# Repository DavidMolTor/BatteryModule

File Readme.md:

# USB-C Battery Module

A compact and reliable power module for battery-powered electronics.

## Introduction

This module is designed to be used in guitars and effect pedals as a rechargeable supply with minimal output voltage ripple.

The module contains a TP4056 charging IC and a voltage regulation stage consisting of a TLV61048 boost converter and a TLV76701 linear regulator for further smoothing of the output voltage.

It is designed for 9V output voltage, although it can be configured by adjusting a couple of resistor dividers. It also has PH connectors for charging, battery and output to be able to adapt it to different use cases.

## Features

 - Independent voltage monitor for overdischarge control.

 - 9V output configurable via resistor dividers.

 - Available pin for battery disconnection.

 - LED indicators for charging status display.

 - Soldered USB-C connector for charging.

 - PH connectors for battery, charging and output.

 - Large package sizes for easy hand-soldering.

 - Tested continuous 500mA output and 1A charging current.

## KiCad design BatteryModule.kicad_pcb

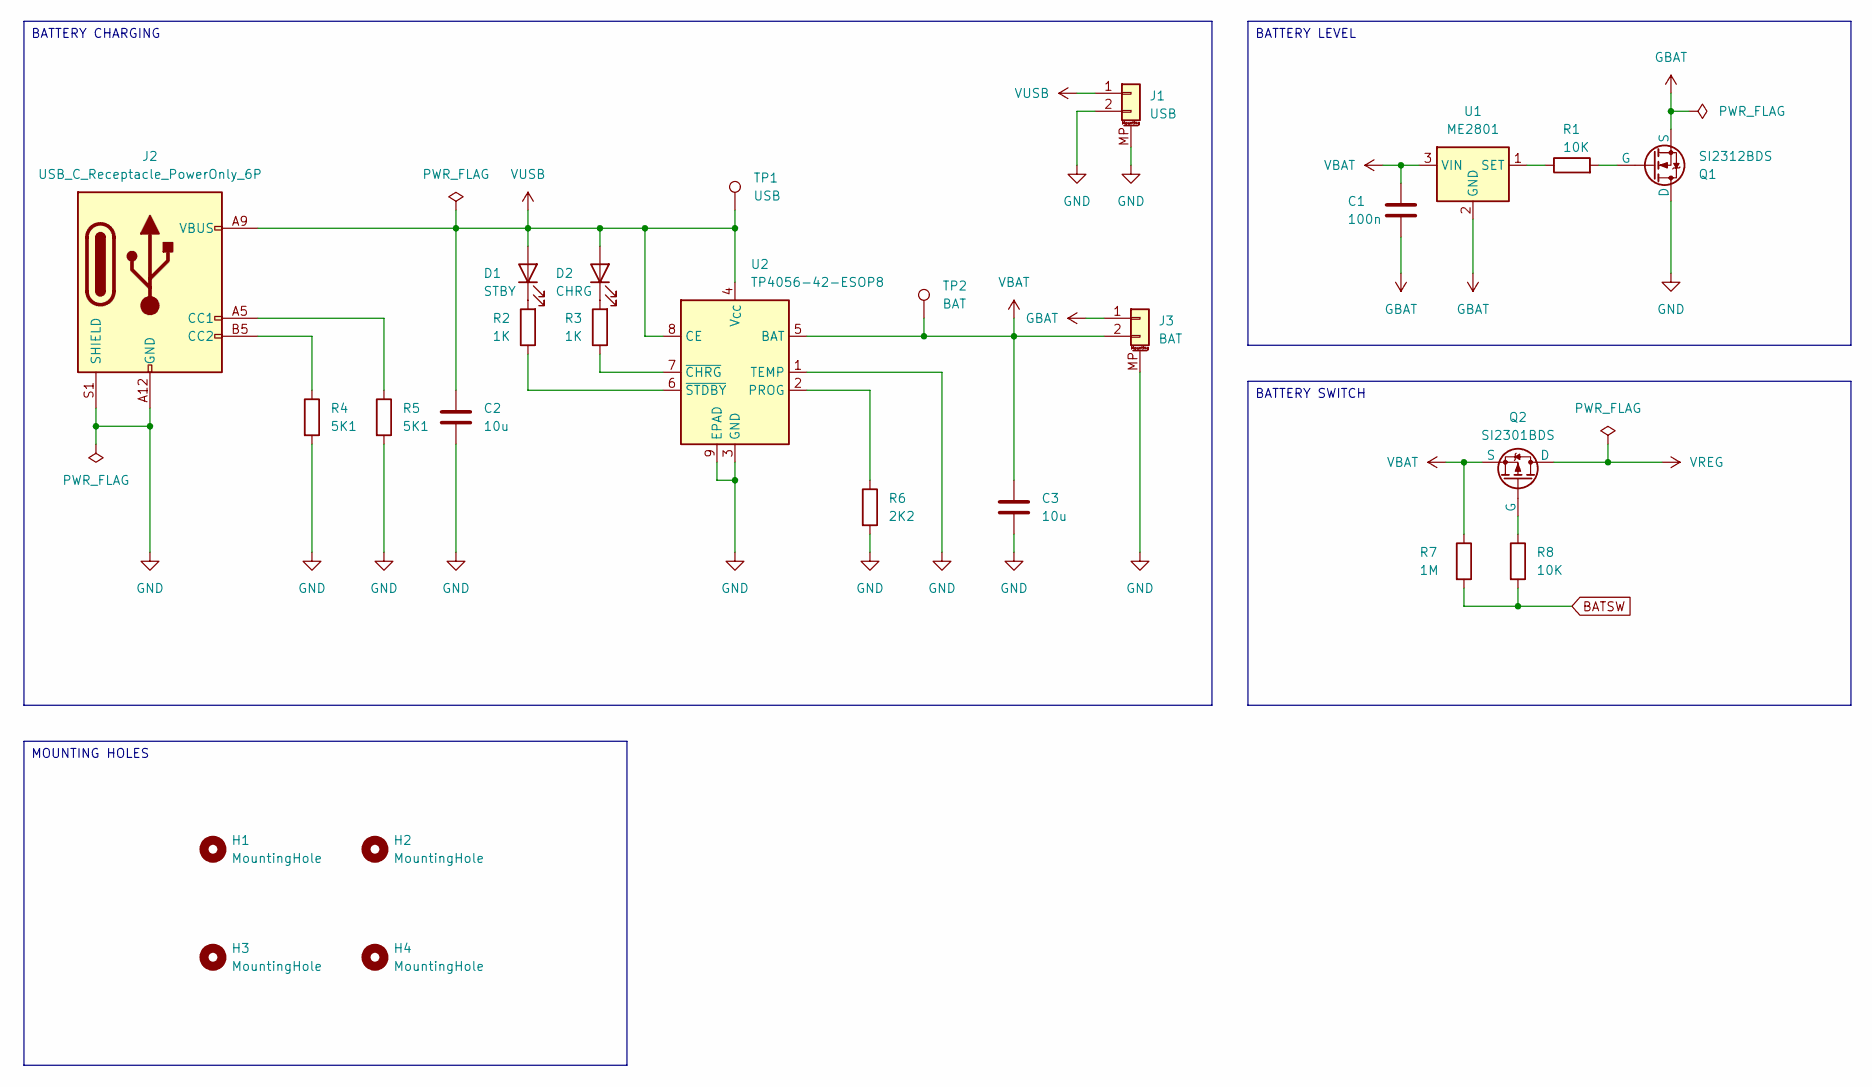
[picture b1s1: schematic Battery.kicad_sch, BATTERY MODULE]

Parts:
C1: 100n; C_0805_2012Metric
C2, C3: 10u; C_1206_3216Metric
D1: STBY; LED_0805_2012Metric
D2: CHRG; LED_0805_2012Metric
H1, H2, H3, H4: MountingHole; MountingHole_3.2mm_M3
J1: USB; JST_PH_1x02_P2.00MM_SMD_HOR
J2: USB_C_Receptacle_PowerOnly_6P; USB_C_Receptacle_GCT_USB4125-xx-x_6P_TopMnt_Horizontal
J3: BAT; JST_PH_1x02_P2.00MM_SMD_HOR
Q1: SI2312BDS; SOT-23_NO_MARK
Q2: SI2301BDS; SOT-23_NO_MARK
R1, R8: 10K; R_0805_2012Metric
R2, R3: 1K; R_0805_2012Metric
R4, R5: 5K1; R_0805_2012Metric
R6: 2K2; R_0805_2012Metric
R7: 1M; R_0805_2012Metric
TP1: USB; TestPoint_Pad_D1.0mm
TP2: BAT; TestPoint_Pad_D1.0mm
U1: ME2801; SOT-23_NO_MARK
U2: TP4056-42-ESOP8; SOIC-8-1EP_3.9x4.9MM_P1.27MM_EP2.41x3.3MM

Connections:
BATSW: R7.2, R8.2; also elsewhere on the board
GBAT: C1.2, J3.1, Q1.2 (S), U1.2 (GND)
GND: C2.2, C3.2, J1.2, J1.MP (MountPin), J2.A12 (GND), J2.B12 (GND), J2.S1 (SHIELD), J3.MP (MountPin), Q1.3 (D), R4.2, R5.2, R6.2, U2.1 (TEMP), U2.3 (GND), U2.9 (EPAD); also elsewhere on the board
unnamed: D1.1 (K), R2.2
unnamed: D2.1 (K), R3.2
unnamed: J2.A5 (CC1), R5.1
unnamed: J2.B5 (CC2), R4.1
unnamed: Q1.1 (G), R1.2
unnamed: Q2.1 (G), R8.1
unnamed: R1.1, U1.1 (SET)
unnamed: R6.1, U2.2 (PROG)
unnamed: R3.1, U2.7 (~CHRG)
unnamed: R2.1, U2.6 (~STDBY)
VBAT: C1.1, C3.1, J3.2, Q2.2 (S), R7.1, TP2.1, U1.3 (VIN), U2.5 (BAT)
VREG: Q2.3 (D); also elsewhere on the board
VUSB: C2.1, D1.2 (A), D2.2 (A), J1.1, J2.A9 (VBUS), J2.B9 (VBUS), TP1.1, U2.4 (V_{CC}), U2.8 (CE)

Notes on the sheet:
BATTERY LEVEL
MOUNTING HOLES
BATTERY SWITCH
BATTERY CHARGING

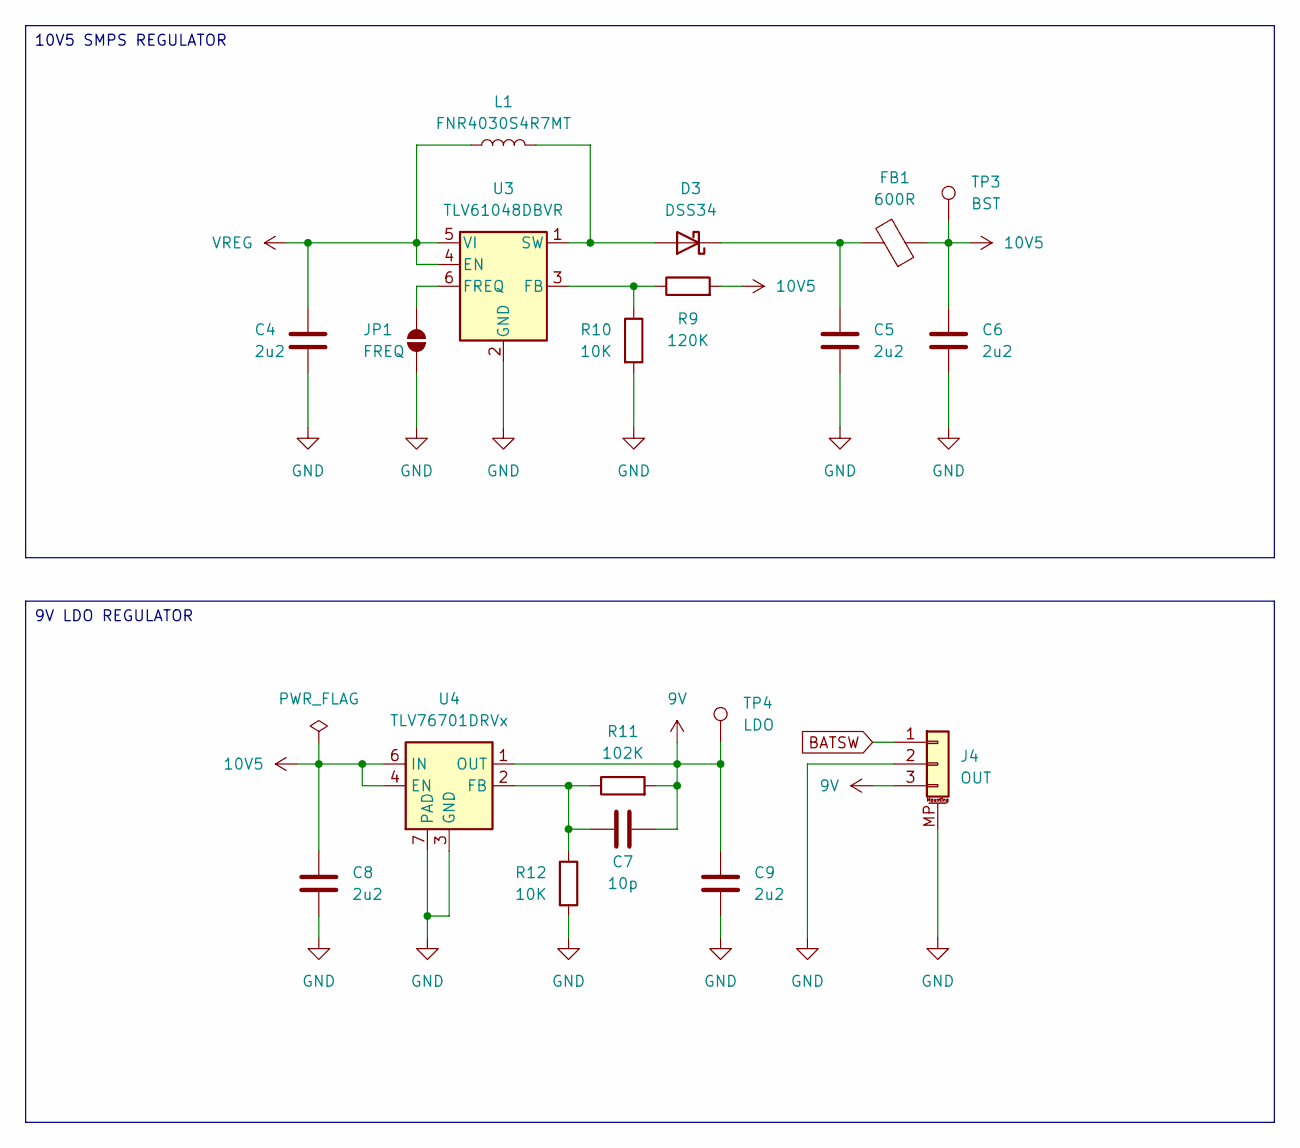
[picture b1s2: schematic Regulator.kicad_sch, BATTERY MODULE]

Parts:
C4, C5, C6, C8, C9: 2u2; C_1206_3216Metric
C7: 10p; C_0805_2012Metric
D3: DSS34; D_SOD-123F
FB1: 600R; L_0805_2012Metric
J4: OUT; JST_PH_1x03_P2.00MM_SMD_HOR
JP1: FREQ; SolderJumper-2_P1.3mm_Open_RoundedPad1.0x1.5mm
L1: FNR4030S4R7MT; L_Changjiang_FNR4030S
R9: 120K; R_0805_2012Metric
R10, R12: 10K; R_0805_2012Metric
R11: 102K; R_0805_2012Metric
TP3: BST; TestPoint_Pad_D1.0mm
TP4: LDO; TestPoint_Pad_D1.0mm
U3: TLV61048DBVR; SOT-23-6
U4: TLV76701DRVx; WSON-6-1EP_2x2mm_P0.65mm_EP1x1.6mm_ThermalVias

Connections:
9V: C7.2, C9.1, J4.3, R11.2, TP4.1, U4.1 (OUT)
10V5: C6.1, C8.1, FB1.1, R9.2, TP3.1, U4.4 (EN), U4.6 (IN)
BATSW: J4.1; also elsewhere on the board
GND: C4.2, C5.2, C6.2, C8.2, C9.2, J4.2, J4.MP (MountPin), JP1.1 (A), R10.2, R12.2, U3.2 (GND), U4.3 (GND), U4.5 (GND), U4.7 (PAD); also elsewhere on the board
unnamed: D3.2 (A), L1.2, U3.1 (SW)
unnamed: C5.1, D3.1 (K), FB1.2
unnamed: JP1.2 (B), U3.6 (FREQ)
unnamed: R9.1, R10.1, U3.3 (FB)
unnamed: C7.1, R11.1, R12.1, U4.2 (FB)
VREG: C4.1, L1.1, U3.4 (EN), U3.5 (VI); also elsewhere on the board

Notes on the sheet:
10V5 SMPS REGULATOR
9V LDO REGULATOR

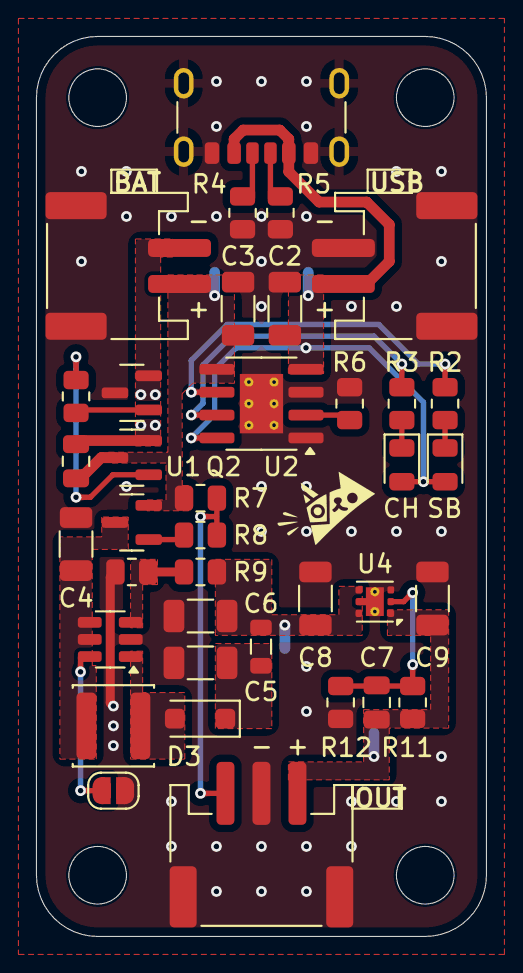
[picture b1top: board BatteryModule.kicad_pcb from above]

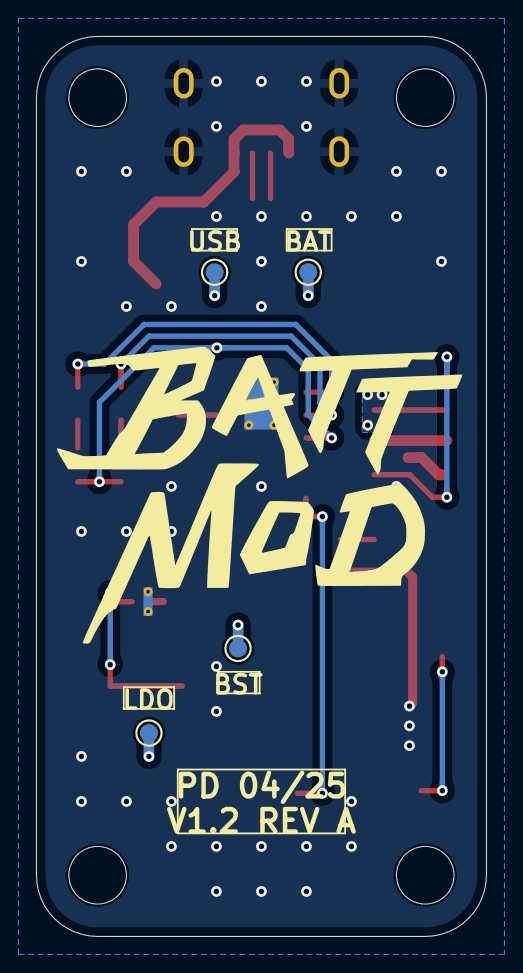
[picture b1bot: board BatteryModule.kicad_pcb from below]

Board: 2 copper layers, 25.0 x 50.0 mm, 45 parts (4 on the bottom side), 23 nets.

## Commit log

2025-06-28 Initial commit
    Added main project files.
2025-06-28 Modified design structure
    Added a battery sheet for the schematic.
    Added a regulator sheet for the schematic.
    Updated board layout.
2025-06-28 Schematic and board layout
    Updated the project schematic.
    Updated the board layout.
2025-07-06 Board picture
    Added a picture of the board render.
2025-07-06 Readme
    Added a readme file for the project.
2025-07-06 Updated readme
    Renamed the readme file.
